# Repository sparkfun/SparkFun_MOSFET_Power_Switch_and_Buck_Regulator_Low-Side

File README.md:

SparkFun MOSFET Power Switch and Buck Regulator (Low-Side)
========================================

[*SparkFun MOSFET Power Switch and Buck Regulator (Low-Side) (COM-23979)*](https://www.sparkfun.com/products/23979)

Does your microcontroller need to control a high-voltage item, like a 12V LED strip, while also needing to be powered? Do you want to avoid having multiple power adapters and microcontrollers for your project? The MOSFET Power Switch and Buck Regulator (Low-Side) is one product we needed at SparkFun, so we figured other folks might have the same problem. Power the board with up to 12V and control up to 10A, all while providing a sweet 3.3V to your control board.

The SparkFun MOSFET Power Switch and Buck Regulator (Low-Side) combines two circuits into one board: an LMR14203 buck regulator configured to output 3.3V and an N-channel MOSFET (PSMN7R0-100BS) configured as a low-side switch. A flyback diode is also on the load side for devices with back EMF! Simply pull the CTL pin low to activate the load.

Various connectors (barrel jack, female header, and poke-home) are provided to connect a power supply to a microcontroller of your choice (Arduino, micro-bit, Raspberry Pi’s microcontroller) and load them together. VCC, 3.3V, CTL, and GND are also broken out through 0.1" spaced PTHs for those who prefer to solder. Two LEDs (PWR_LED and ON_LED) indicate when there is 3.3V and whenever power is applied to the load. Jumpers are included on the back to disable the LEDs. A MEAS PTH jumper is also included for those interested in precisely measuring the current consumption of the system.

_**Note:** While the MOSFET is rated to 100A/100V, we don't recommend you go much above 10A as the PCB polygon pours and traces become the limiter._

Repository Contents
-------------------

* **.github/workflows** -  YAML files used for GitHub Actions and GitHub Pages/mkdocs
* * **/Firmware** - Basic example code to control a load with the MOSFET Power Switch and BUck Regulator
* **/Hardware** - Eagle design files (.brd, .sch)
  * **/Production** - Production panel files (.brd)
* **/docs** - Online documentation files for GitHub Pages and mkdocs
  * **/assets** - Folder containing all the file assets used for product documentation
    * **/board_files** - Copy of design files used for product documentation
    * **/component_documentation** - Datasheets and manuals for hardware components
    * **/img** - Images for product documentation
  * **/github** - Files stating how to contribute and filing issues for product
  * **/javascript** - Folder containing custom javascript used for product documentation
  * **/stylesheet** - Folder containing CSS files used forproduct documentation
* **/overrides** - Customization files used for product documentation
  * **/.icons** - Icons used for product documentation
  * **./partials** - Used for product documentation

Documentation
--------------

* **[Fritzing Part](https://github.com/sparkfun/Fritzing_Parts/blob/main/products/23979_sfe_n-channel_mosfet_power_switch_buck_regulator_low-side_transistor.fzpz)**
* **[Hookup Guide](https://docs.sparkfun.com/SparkFun_MOSFET_Power_Switch_and_Buck_Regulator_Low-Side)** - Basic hookup guide for the MOSFET Power Switch and Buck Regulator (Low-Side).

Product Versions
----------------

* [COM-23979](https://www.sparkfun.com/products/23979) - Initial SparkFun release, v1.1
* [SPX-19799](https://www.sparkfun.com/products/19799) - SparkX version

Version History
---------------
* v1.1 - Initial release

License Information
-------------------

This product is _**open source**_! 

Please review the LICENSE.md file for license information. 

If you have any questions or concerns on licensing, please contact technical support on our [SparkFun forums](https://forum.sparkfun.com/viewforum.php?f=152).

Distributed as-is; no warranty is given.

- Your friends at SparkFun.

_<COLLABORATION CREDIT>_

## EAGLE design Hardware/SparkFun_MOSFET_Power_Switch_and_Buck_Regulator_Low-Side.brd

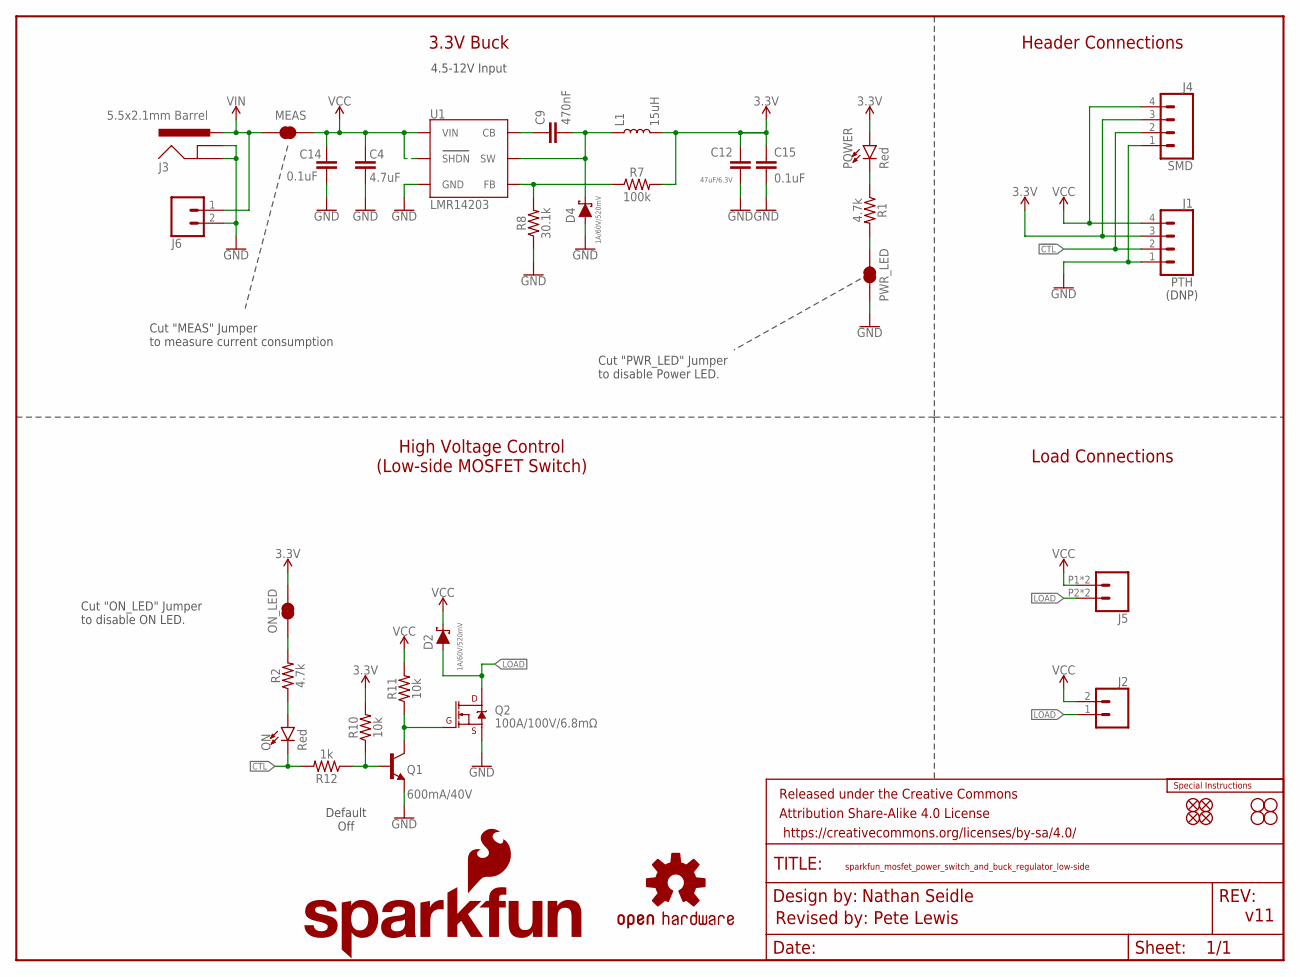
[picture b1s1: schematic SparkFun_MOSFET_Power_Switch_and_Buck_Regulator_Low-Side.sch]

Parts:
C4: 4.7uF; 0603
C9: 470nF; 0603
C12: 47uF/6.3V; 0805
C14, C15: 0.1uF; 0603
D2, D4: 1A/60V/520mV; DIODE-MICRO-SMP
FD1, FD2, FD3, FD4: FIDUCIALUFIDUCIAL; FIDUCIAL-MICRO
FRAME2: FRAME-LETTER; CREATIVE_COMMONS
H1, H2, H3, H4: STAND-OFF
J1: PTH; 1X04_NO_SILK
J2, J6: CONN_021X02_NO_SILK; 1X02_NO_SILK
J3: 5.5x2.1mm Barrel; POWER_JACK_SMD
J4: SMD; 1X04_SMD_VERTICAL_COMBO
J5: CONN_02SMALL_POKEHOME; 1X02_POKEHOME
L1: 15uH; INDUCTOR_LQH32
LOGO1: OSHW-LOGOM; OSHW-LOGO-M
LOGO2: SFE_LOGO_NAME_FLAME.2_INCH; SFE_LOGO_NAME_FLAME_.2
LOGO3: SPECIAL_INSTRUCTIONS-ORDERING; ORDERING_INSTRUCTIONS
MEAS: JUMPER-COMBO_2_NC_TRACE; COMBO-JUMPER_2_NC_TRACE
ON: Red; LED-0603
ON_LED: JUMPER-SMT_2_NC_TRACE_SILK; SMT-JUMPER_2_NC_TRACE_SILK
POWER: Red; LED-0603
PWR_LED: JUMPER-SMT_2_NC_TRACE_SILK; SMT-JUMPER_2_NC_TRACE_SILK
Q1: 600mA/40V; SOT23-3
Q2: 100A/100V/6.8mΩ; TO-263/D2PAK
R1, R2: 4.7k; 0603
R7: 100k; 0603
R8: 30.1k; 0603
R10, R11: 10k; 0603
R12: 1k; 0603
U1: LMR14203; SOT23-6

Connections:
3.3V: C12.1, C15.1, J1.3, J4.3, L1.P$2 (2), ON_LED.2, POWER.A, R7.2, R10.2
!CTL: J1.2, J4.2, ON.C, R12.2
GND: C4.2, C12.2, C14.2, C15.2, D4.A, J1.1, J3.GND (GNDBREAK), J3.P$4 (GND), J4.1, J6.2, PWR_LED.1, Q1.2 (E), Q2.3 (S), R8.1, U1.2 (GND)
LOAD: D2.A, J2.1, J5.P2 (2), J5.P4 (2), Q2.2 (D)
unnamed: Q1.3 (C), Q2.1 (G), R11.1
unnamed: ON.A, R2.1
unnamed: POWER.C, R1.1
unnamed: R7.1, R8.2, U1.3 (FB)
unnamed: PWR_LED.2, R1.2
unnamed: ON_LED.1, R2.2
unnamed: C9.1, U1.1 (CB)
unnamed: Q1.1 (B), R10.1, R12.1
VCC: C4.1, C14.1, D2.C, J1.4, J2.2, J4.4, J5.P1 (1), J5.P3 (1), MEAS.2, MEAS.4 (2), R11.2, U1.4 (SHDN), U1.5 (VIN)
VIN: J3.VIN0 (PWR), J6.1, MEAS.1, MEAS.3 (1)
VSW: C9.2, D4.C, L1.P$1 (1), U1.6 (SW)

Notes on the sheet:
v11
Default Off
Load Connections
High Voltage Control (Low-side MOSFET Switch)
3.3V Buck
4.5-12V Input
Nathan Seidle
Revised by: Pete Lewis
Header Connections
Cut "ON_LED" Jumper to disable ON LED.
Cut "PWR_LED" Jumper to disable Power LED.
(DNP)
Cut "MEAS" Jumper to measure current consumption

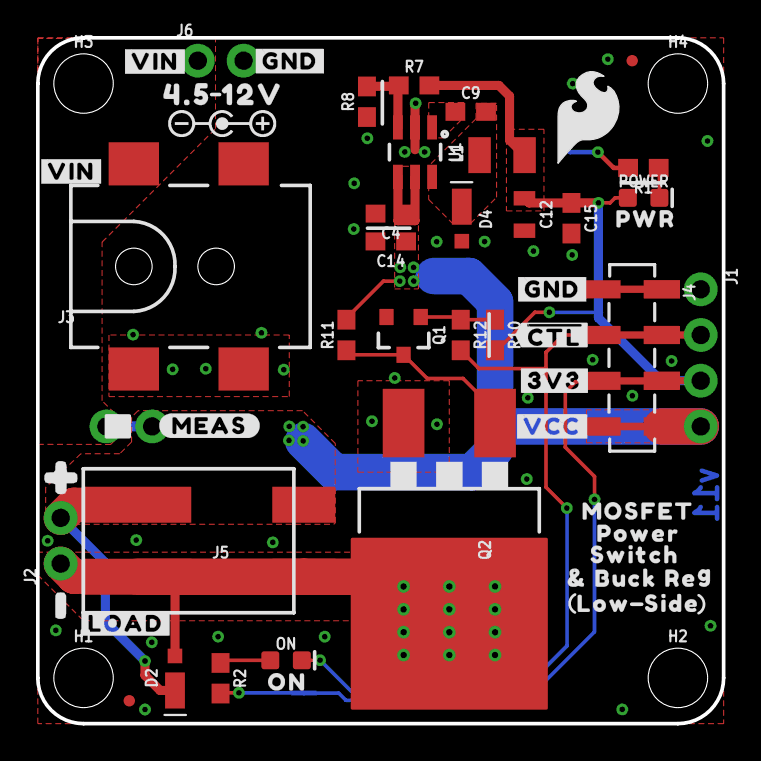
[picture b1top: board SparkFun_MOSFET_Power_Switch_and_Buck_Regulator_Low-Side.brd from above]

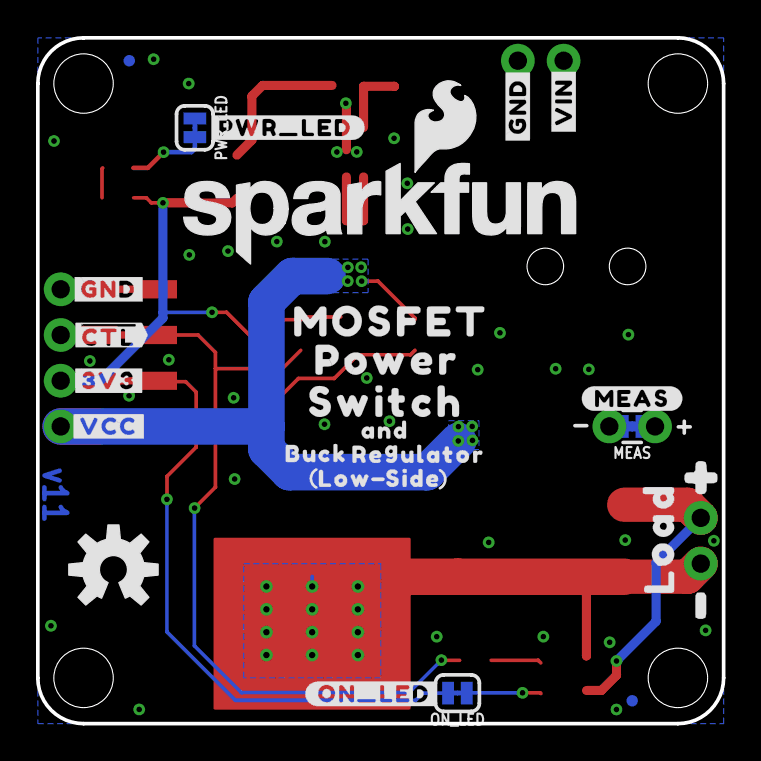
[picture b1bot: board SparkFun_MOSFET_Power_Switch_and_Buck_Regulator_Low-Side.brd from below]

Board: 2 copper layers, 38.1 x 38.1 mm, 83 parts (27 on the bottom side), 15 nets.

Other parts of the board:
U$1: #LOAD#7
U$2: MOSFET0
U$3, U$21, U$36: #VIN#8
U$4, U$6, U$12, U$37: #GND#0
U$8: SFE_LOGO_FLAME_.2
U$9: POWER1
U$10, U$20: #0
U$11, U$22: #1
U$13: SWITCH2
U$14, U$27: #3V3#3
U$15: #PWR_LED#11
U$16: #ON_LED#13
U$17, U$38: #MEAS#14
U$18: 4#5_12V5
U$19: LOAD0
U$23, U$43: LOW0
U$24: MOSFET_0
U$25: POWER_1
U$26: SWITCH_2
U$28: ##CTL##1
U$29: POLARITY_MARKING_CENTER_POSITIVE#JPG
U$30: ##CTL##2
U$31, U$32: #VCC#4
U$33, U$44: SIDE0
U$34: PWR9
U$35: ON10
U$39: BUCK5
U$40: REGULATOR6
U$41: #_BUCK_REG7
U$42: AND8

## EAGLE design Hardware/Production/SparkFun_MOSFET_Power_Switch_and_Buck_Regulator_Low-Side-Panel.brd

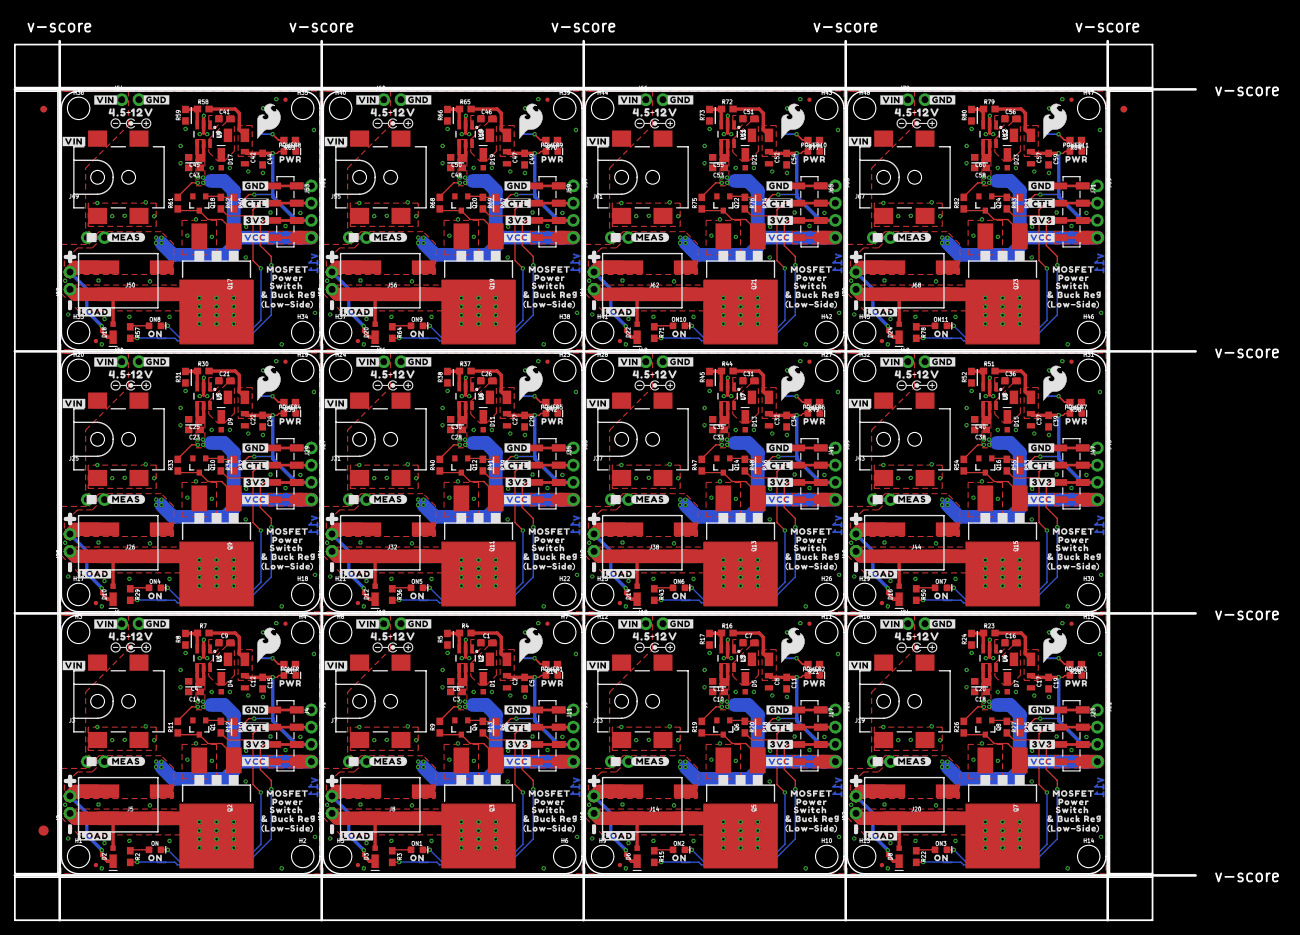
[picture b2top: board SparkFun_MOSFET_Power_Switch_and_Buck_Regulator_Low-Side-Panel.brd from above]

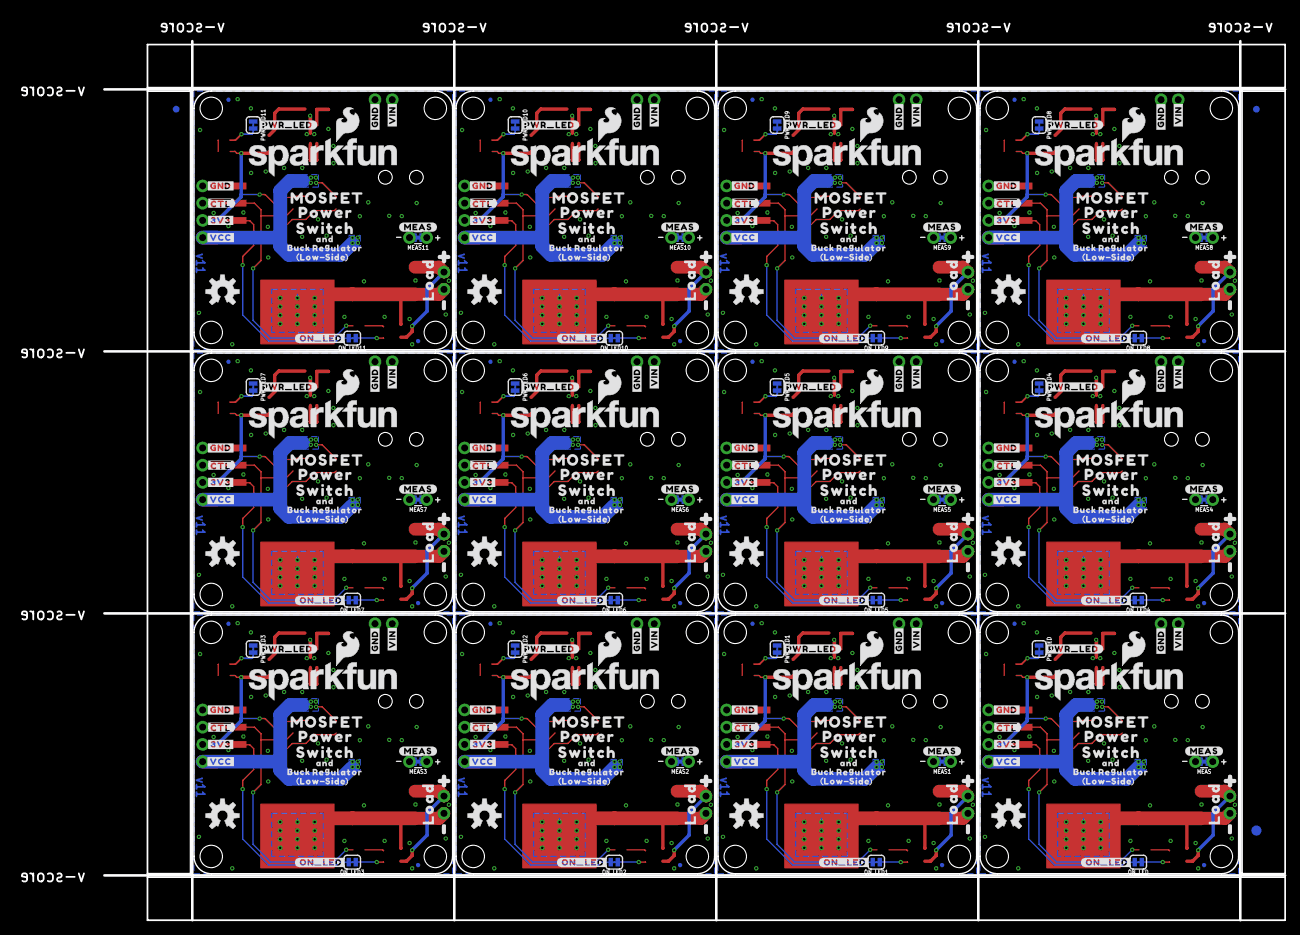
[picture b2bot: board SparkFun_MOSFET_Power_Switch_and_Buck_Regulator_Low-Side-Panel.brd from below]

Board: 2 copper layers, 174.0 x 129.5 mm, 978 parts (327 on the bottom side), 180 nets.

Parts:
C1, C7, C9, C16, C21, C26, C31, C36, C41, C46, C51, C56: 470nF; 0603
C2, C8, C12, C17, C22, C27, C32, C37, C42, C47, C52, C57: 47uF/6.3V; 0805
C3, C5, C10, C11, C14, C15, C18, C19, C23, C24, C28, C29, C33, C34, C38, C39, C43, C44, C48, C49, C53, C54, C58, C59: 0.1uF; 0603
C4, C6, C13, C20, C25, C30, C35, C40, C45, C50, C55, C60: 4.7uF; 0603
D1, D2, D3, D4, D5, D6, D7, D8, D9, D10, D11, D12, D13, D14, D15, D16, D17, D18, D19, D20, D21, D22, D23, D24: 1A/60V/520mV; DIODE-MICRO-SMP
E$1, E$2, E$3, E$4: FIDUCIAL-1X2
E$5, E$6: FIDUCIAL-1.5X3
FD1, FD2, FD3, FD4, FD5, FD6, FD7, FD8, FD9, FD10, FD11, FD12, FD13, FD14, FD15, FD16, FD17, FD18, FD19, FD20, FD21, FD22, FD23, FD24, FD25, FD26, FD27, FD28, FD29, FD30, FD31, FD32, FD33, FD34, FD35, FD36, FD37, FD38, FD39, FD40, FD41, FD42, FD43, FD44, FD45, FD46, FD47, FD48: FIDUCIALUFIDUCIAL; FIDUCIAL-MICRO
H1, H2, H3, H4, H5, H6, H7, H8, H9, H10, H11, H12, H13, H14, H15, H16, H17, H18, H19, H20, H21, H22, H23, H24, H25, H26, H27, H28, H29, H30, H31, H32, H33, H34, H35, H36, H37, H38, H39, H40, H41, H42, H43, H44, H45, H46, H47, H48: STAND-OFF
J1, J9, J15, J21, J27, J33, J39, J45, J51, J57, J63, J69: PTH; 1X04_NO_SILK
J2, J6, J10, J12, J16, J18, J22, J24, J28, J30, J34, J36, J40, J42, J46, J48, J52, J54, J58, J60, J64, J66, J70, J72: 1X02_NO_SILK
J3, J7, J13, J19, J25, J31, J37, J43, J49, J55, J61, J67: 5.5x2.1mm Barrel; POWER_JACK_SMD
J4, J11, J17, J23, J29, J35, J41, J47, J53, J59, J65, J71: SMD; 1X04_SMD_VERTICAL_COMBO
J5, J8, J14, J20, J26, J32, J38, J44, J50, J56, J62, J68: 1X02_POKEHOME
L1, L2, L3, L4, L5, L6, L7, L8, L9, L10, L11, L12: 15uH; INDUCTOR_LQH32
LOGO1, LOGO3, LOGO5, LOGO7, LOGO9, LOGO11, LOGO13, LOGO15, LOGO17, LOGO19, LOGO21, LOGO23: OSHW-LOGOM; OSHW-LOGO-M
LOGO2, LOGO4, LOGO6, LOGO8, LOGO10, LOGO12, LOGO14, LOGO16, LOGO18, LOGO20, LOGO22, LOGO24: SFE_LOGO_NAME_FLAME.2_INCH; SFE_LOGO_NAME_FLAME_.2
MEAS, MEAS1, MEAS2, MEAS3, MEAS4, MEAS5, MEAS6, MEAS7, MEAS8, MEAS9, MEAS10, MEAS11: JUMPER-COMBO_2_NC_TRACE; COMBO-JUMPER_2_NC_TRACE
ON, ON1, ON2, ON3, ON4, ON5, ON6, ON7, ON8, ON9, ON10, ON11: Red; LED-0603
ON_LED, ON_LED1, ON_LED2, ON_LED3, ON_LED4, ON_LED5, ON_LED6, ON_LED7, ON_LED8, ON_LED9, ON_LED10, ON_LED11: SMT-JUMPER_2_NC_TRACE_SILK
POWER, POWER1, POWER2, POWER3, POWER4, POWER5, POWER6, POWER7, POWER8, POWER9, POWER10, POWER11: Red; LED-0603
PWR_LED, PWR_LED1, PWR_LED2, PWR_LED3, PWR_LED4, PWR_LED5, PWR_LED6, PWR_LED7, PWR_LED8, PWR_LED9, PWR_LED10, PWR_LED11: SMT-JUMPER_2_NC_TRACE_SILK
Q1, Q4, Q6, Q8, Q10, Q12, Q14, Q16, Q18, Q20, Q22, Q24: 600mA/40V; SOT23-3
Q2, Q3, Q5, Q7, Q9, Q11, Q13, Q15, Q17, Q19, Q21, Q23: 100A/100V/6.8mΩ; TO-263/D2PAK
R1, R2, R3, R14, R15, R21, R22, R28, R29, R35, R36, R42, R43, R49, R50, R56, R57, R63, R64, R70, R71, R77, R78, R84: 4.7k; 0603
R4, R7, R16, R23, R30, R37, R44, R51, R58, R65, R72, R79: 100k; 0603
R5, R8, R17, R24, R31, R38, R45, R52, R59, R66, R73, R80: 30.1k; 0603
R6, R9, R10, R11, R18, R19, R25, R26, R32, R33, R39, R40, R46, R47, R53, R54, R60, R61, R67, R68, R74, R75, R81, R82: 10k; 0603
R12, R13, R20, R27, R34, R41, R48, R55, R62, R69, R76, R83: 1k; 0603
U1, U2, U3, U4, U5, U6, U7, U8, U9, U10, U11, U12: LMR14203; SOT23-6
U$1, U$63, U$105, U$147, U$189, U$231, U$273, U$315, U$357, U$399, U$441, U$483: #LOAD#7
U$2, U$49, U$91, U$133, U$175, U$217, U$259, U$301, U$343, U$385, U$427, U$469: MOSFET0
U$3, U$21, U$36, U$64, U$71, U$75, U$106, U$113, U$117, U$148, U$155, U$159, U$190, U$197, U$201, U$232, U$239, U$243, U$274, U$281, U$285, U$316, U$323, U$327, U$358, U$365, U$369, U$400, U$407, U$411, U$442, U$449, U$453, U$484, U$491, U$495: #VIN#8
U$4, U$6, U$12, U$37, U$55, U$56, U$72, U$74, U$97, U$98, U$114, U$116, U$139, U$140, U$156, U$158, U$181, U$182, U$198, U$200, U$223, U$224, U$240, U$242, U$265, U$266, U$282, U$284, U$307, U$308, U$324, U$326, U$349, U$350, U$366, U$368, U$391, U$392, U$408, U$410, U$433, U$434, U$450, U$452, U$475, U$476, U$492, U$494: #GND#0
U$5, U$29, U$85, U$127, U$169, U$211, U$253, U$295, U$337, U$379, U$421, U$463: POLARITY_MARKING_CENTER_POSITIVE#JPG
U$7, U$10, U$20, U$47, U$86, U$89, U$128, U$131, U$170, U$173, U$212, U$215, U$254, U$257, U$296, U$299, U$338, U$341, U$380, U$383, U$422, U$425, U$464, U$467: #0
U$8, U$65, U$107, U$149, U$191, U$233, U$275, U$317, U$359, U$401, U$443, U$485: SFE_LOGO_FLAME_.2
U$9, U$50, U$92, U$134, U$176, U$218, U$260, U$302, U$344, U$386, U$428, U$470: POWER1
U$11, U$22, U$45, U$48, U$87, U$90, U$129, U$132, U$171, U$174, U$213, U$216, U$255, U$258, U$297, U$300, U$339, U$342, U$381, U$384, U$423, U$426, U$465, U$468: #1
U$13, U$51, U$93, U$135, U$177, U$219, U$261, U$303, U$345, U$387, U$429, U$471: SWITCH2
U$14, U$27, U$59, U$60, U$101, U$102, U$143, U$144, U$185, U$186, U$227, U$228, U$269, U$270, U$311, U$312, U$353, U$354, U$395, U$396, U$437, U$438, U$479, U$480: #3V3#3
U$15, U$66, U$108, U$150, U$192, U$234, U$276, U$318, U$360, U$402, U$444, U$486: #PWR_LED#11
U$16, U$67, U$109, U$151, U$193, U$235, U$277, U$319, U$361, U$403, U$445, U$487: #ON_LED#13
U$17, U$38, U$68, U$76, U$110, U$118, U$152, U$160, U$194, U$202, U$236, U$244, U$278, U$286, U$320, U$328, U$362, U$370, U$404, U$412, U$446, U$454, U$488, U$496: #MEAS#14
U$18, U$73, U$115, U$157, U$199, U$241, U$283, U$325, U$367, U$409, U$451, U$493: 4#5_12V5
U$19, U$46, U$88, U$130, U$172, U$214, U$256, U$298, U$340, U$382, U$424, U$466: LOAD0
U$23, U$43, U$69, U$81, U$111, U$123, U$153, U$165, U$195, U$207, U$237, U$249, U$279, U$291, U$321, U$333, U$363, U$375, U$405, U$417, U$447, U$459, U$489, U$501: LOW0
U$24, U$52, U$94, U$136, U$178, U$220, U$262, U$304, U$346, U$388, U$430, U$472: MOSFET_0
U$25, U$53, U$95, U$137, U$179, U$221, U$263, U$305, U$347, U$389, U$431, U$473: POWER_1
U$26, U$54, U$96, U$138, U$180, U$222, U$264, U$306, U$348, U$390, U$432, U$474: SWITCH_2
U$28, U$57, U$99, U$141, U$183, U$225, U$267, U$309, U$351, U$393, U$435, U$477: ##CTL##1
U$30, U$58, U$100, U$142, U$184, U$226, U$268, U$310, U$352, U$394, U$436, U$478: ##CTL##2
U$31, U$32, U$61, U$62, U$103, U$104, U$145, U$146, U$187, U$188, U$229, U$230, U$271, U$272, U$313, U$314, U$355, U$356, U$397, U$398, U$439, U$440, U$481, U$482: #VCC#4
U$33, U$44, U$70, U$82, U$112, U$124, U$154, U$166, U$196, U$208, U$238, U$250, U$280, U$292, U$322, U$334, U$364, U$376, U$406, U$418, U$448, U$460, U$490, U$502: SIDE0
U$34, U$83, U$125, U$167, U$209, U$251, U$293, U$335, U$377, U$419, U$461, U$503: PWR9
U$35, U$84, U$126, U$168, U$210, U$252, U$294, U$336, U$378, U$420, U$462, U$504: ON10
U$39, U$77, U$119, U$161, U$203, U$245, U$287, U$329, U$371, U$413, U$455, U$497: BUCK5
U$40, U$78, U$120, U$162, U$204, U$246, U$288, U$330, U$372, U$414, U$456, U$498: REGULATOR6
U$41, U$79, U$121, U$163, U$205, U$247, U$289, U$331, U$373, U$415, U$457, U$499: #_BUCK_REG7
U$42, U$80, U$122, U$164, U$206, U$248, U$290, U$332, U$374, U$416, U$458, U$500: AND8

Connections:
3.3V: C12.1, C15.1, J1.3, J4.3, L1.P$2, ON_LED.2, POWER.A, R7.2, R10.2
3.3V1: C2.1, C5.1, J9.3, J11.3, L2.P$2, ON_LED1.2, POWER1.A, R4.2, R6.2
3.3V2: C8.1, C11.1, J15.3, J17.3, L3.P$2, ON_LED2.2, POWER2.A, R16.2, R18.2
3.3V3: C17.1, C19.1, J21.3, J23.3, L4.P$2, ON_LED3.2, POWER3.A, R23.2, R25.2
3.3V4: C22.1, C24.1, J27.3, J29.3, L5.P$2, ON_LED4.2, POWER4.A, R30.2, R32.2
3.3V5: C27.1, C29.1, J33.3, J35.3, L6.P$2, ON_LED5.2, POWER5.A, R37.2, R39.2
3.3V6: C32.1, C34.1, J39.3, J41.3, L7.P$2, ON_LED6.2, POWER6.A, R44.2, R46.2
3.3V7: C37.1, C39.1, J45.3, J47.3, L8.P$2, ON_LED7.2, POWER7.A, R51.2, R53.2
3.3V8: C42.1, C44.1, J51.3, J53.3, L9.P$2, ON_LED8.2, POWER8.A, R58.2, R60.2
3.3V9: C47.1, C49.1, J57.3, J59.3, L10.P$2, ON_LED9.2, POWER9.A, R65.2, R67.2
3.3V10: C52.1, C54.1, J63.3, J65.3, L11.P$2, ON_LED10.2, POWER10.A, R72.2, R74.2
3.3V11: C57.1, C59.1, J69.3, J71.3, L12.P$2, ON_LED11.2, POWER11.A, R79.2, R81.2
!CTL: J1.2, J4.2, ON.C, R12.2
!CTL1: J9.2, J11.2, ON1.C, R13.2
!CTL2: J15.2, J17.2, ON2.C, R20.2
!CTL3: J21.2, J23.2, ON3.C, R27.2
!CTL4: J27.2, J29.2, ON4.C, R34.2
!CTL5: J33.2, J35.2, ON5.C, R41.2
!CTL6: J39.2, J41.2, ON6.C, R48.2
!CTL7: J45.2, J47.2, ON7.C, R55.2
!CTL8: J51.2, J53.2, ON8.C, R62.2
!CTL9: J57.2, J59.2, ON9.C, R69.2
!CTL10: J63.2, J65.2, ON10.C, R76.2
!CTL11: J69.2, J71.2, ON11.C, R83.2
GND: C4.2, C12.2, C14.2, C15.2, D4.A, J1.1, J3.GND, J3.P$4, J4.1, J6.2, PWR_LED.1, Q1.2, Q2.3, R8.1, U1.2
GND1: C2.2, C3.2, C5.2, C6.2, D1.A, J7.GND, J7.P$4, J9.1, J11.1, J12.2, PWR_LED1.1, Q3.3, Q4.2, R5.1, U2.2
GND2: C8.2, C10.2, C11.2, C13.2, D5.A, J13.GND, J13.P$4, J15.1, J17.1, J18.2, PWR_LED2.1, Q5.3, Q6.2, R17.1, U3.2
GND3: C17.2, C18.2, C19.2, C20.2, D7.A, J19.GND, J19.P$4, J21.1, J23.1, J24.2, PWR_LED3.1, Q7.3, Q8.2, R24.1, U4.2
GND4: C22.2, C23.2, C24.2, C25.2, D9.A, J25.GND, J25.P$4, J27.1, J29.1, J30.2, PWR_LED4.1, Q9.3, Q10.2, R31.1, U5.2
GND5: C27.2, C28.2, C29.2, C30.2, D11.A, J31.GND, J31.P$4, J33.1, J35.1, J36.2, PWR_LED5.1, Q11.3, Q12.2, R38.1, U6.2
GND6: C32.2, C33.2, C34.2, C35.2, D13.A, J37.GND, J37.P$4, J39.1, J41.1, J42.2, PWR_LED6.1, Q13.3, Q14.2, R45.1, U7.2
GND7: C37.2, C38.2, C39.2, C40.2, D15.A, J43.GND, J43.P$4, J45.1, J47.1, J48.2, PWR_LED7.1, Q15.3, Q16.2, R52.1, U8.2
GND8: C42.2, C43.2, C44.2, C45.2, D17.A, J49.GND, J49.P$4, J51.1, J53.1, J54.2, PWR_LED8.1, Q17.3, Q18.2, R59.1, U9.2
GND9: C47.2, C48.2, C49.2, C50.2, D19.A, J55.GND, J55.P$4, J57.1, J59.1, J60.2, PWR_LED9.1, Q19.3, Q20.2, R66.1, U10.2
GND10: C52.2, C53.2, C54.2, C55.2, D21.A, J61.GND, J61.P$4, J63.1, J65.1, J66.2, PWR_LED10.1, Q21.3, Q22.2, R73.1, U11.2
GND11: C57.2, C58.2, C59.2, C60.2, D23.A, J67.GND, J67.P$4, J69.1, J71.1, J72.2, PWR_LED11.1, Q23.3, Q24.2, R80.1, U12.2
LOAD: D2.A, J2.1, J5.P2, J5.P4, Q2.2
LOAD1: D3.A, J8.P2, J8.P4, J10.1, Q3.2
LOAD2: D6.A, J14.P2, J14.P4, J16.1, Q5.2
LOAD3: D8.A, J20.P2, J20.P4, J22.1, Q7.2
LOAD4: D10.A, J26.P2, J26.P4, J28.1, Q9.2
LOAD5: D12.A, J32.P2, J32.P4, J34.1, Q11.2
LOAD6: D14.A, J38.P2, J38.P4, J40.1, Q13.2
LOAD7: D16.A, J44.P2, J44.P4, J46.1, Q15.2
LOAD8: D18.A, J50.P2, J50.P4, J52.1, Q17.2
LOAD9: D20.A, J56.P2, J56.P4, J58.1, Q19.2
LOAD10: D22.A, J62.P2, J62.P4, J64.1, Q21.2
LOAD11: D24.A, J68.P2, J68.P4, J70.1, Q23.2
unnamed: Q1.3, Q2.1, R11.1
unnamed: ON.A, R2.1
unnamed: POWER.C, R1.1
unnamed: ON1.A, R3.1
unnamed: R7.1, R8.2, U1.3
unnamed: PWR_LED.2, R1.2
unnamed: ON_LED.1, R2.2
unnamed: R4.1, R5.2, U2.3
unnamed: C1.1, U2.1
unnamed: C9.1, U1.1
unnamed: Q3.1, Q4.3, R9.1
unnamed: Q1.1, R10.1, R12.1
unnamed: Q4.1, R6.1, R13.1
unnamed: POWER1.C, R14.1
unnamed: PWR_LED1.2, R14.2
unnamed: ON_LED1.1, R3.2
unnamed: ON2.A, R15.1
unnamed: R16.1, R17.2, U3.3
unnamed: C7.1, U3.1
unnamed: Q5.1, Q6.3, R19.1
unnamed: Q6.1, R18.1, R20.1
unnamed: POWER2.C, R21.1
unnamed: PWR_LED2.2, R21.2
unnamed: ON_LED2.1, R15.2
unnamed: ON3.A, R22.1
unnamed: R23.1, R24.2, U4.3
unnamed: C16.1, U4.1
unnamed: Q7.1, Q8.3, R26.1
unnamed: Q8.1, R25.1, R27.1
unnamed: POWER3.C, R28.1
unnamed: PWR_LED3.2, R28.2
unnamed: ON_LED3.1, R22.2
unnamed: ON4.A, R29.1
unnamed: R30.1, R31.2, U5.3
unnamed: C21.1, U5.1
unnamed: Q9.1, Q10.3, R33.1
unnamed: Q10.1, R32.1, R34.1
unnamed: POWER4.C, R35.1
unnamed: PWR_LED4.2, R35.2
unnamed: ON_LED4.1, R29.2
unnamed: ON5.A, R36.1
unnamed: R37.1, R38.2, U6.3
unnamed: C26.1, U6.1
unnamed: Q11.1, Q12.3, R40.1
unnamed: Q12.1, R39.1, R41.1
unnamed: POWER5.C, R42.1
unnamed: PWR_LED5.2, R42.2
unnamed: ON_LED5.1, R36.2
unnamed: ON6.A, R43.1
unnamed: R44.1, R45.2, U7.3
unnamed: C31.1, U7.1
unnamed: Q13.1, Q14.3, R47.1
unnamed: Q14.1, R46.1, R48.1
unnamed: POWER6.C, R49.1
unnamed: PWR_LED6.2, R49.2
unnamed: ON_LED6.1, R43.2
unnamed: ON7.A, R50.1
unnamed: R51.1, R52.2, U8.3
unnamed: C36.1, U8.1
unnamed: Q15.1, Q16.3, R54.1
unnamed: Q16.1, R53.1, R55.1
unnamed: POWER7.C, R56.1
unnamed: PWR_LED7.2, R56.2
unnamed: ON_LED7.1, R50.2
unnamed: ON8.A, R57.1
unnamed: R58.1, R59.2, U9.3
unnamed: C41.1, U9.1
unnamed: Q17.1, Q18.3, R61.1
unnamed: Q18.1, R60.1, R62.1
unnamed: POWER8.C, R63.1
unnamed: PWR_LED8.2, R63.2
unnamed: ON_LED8.1, R57.2
unnamed: ON9.A, R64.1
unnamed: R65.1, R66.2, U10.3
unnamed: C46.1, U10.1
unnamed: Q19.1, Q20.3, R68.1
unnamed: Q20.1, R67.1, R69.1
unnamed: POWER9.C, R70.1
unnamed: PWR_LED9.2, R70.2
unnamed: ON_LED9.1, R64.2
unnamed: ON10.A, R71.1
unnamed: R72.1, R73.2, U11.3
unnamed: C51.1, U11.1
unnamed: Q21.1, Q22.3, R75.1
unnamed: Q22.1, R74.1, R76.1
unnamed: POWER10.C, R77.1
unnamed: PWR_LED10.2, R77.2
unnamed: ON_LED10.1, R71.2
unnamed: ON11.A, R78.1
unnamed: R79.1, R80.2, U12.3
unnamed: C56.1, U12.1
unnamed: Q23.1, Q24.3, R82.1
unnamed: Q24.1, R81.1, R83.1
unnamed: POWER11.C, R84.1
unnamed: PWR_LED11.2, R84.2
unnamed: ON_LED11.1, R78.2
VCC: C4.1, C14.1, D2.C, J1.4, J2.2, J4.4, J5.P1, J5.P3, MEAS.2, MEAS.4, R11.2, U1.4, U1.5
VCC1: C3.1, C6.1, D3.C, J8.P1, J8.P3, J9.4, J10.2, J11.4, MEAS1.2, MEAS1.4, R9.2, U2.4, U2.5
VCC2: C10.1, C13.1, D6.C, J14.P1, J14.P3, J15.4, J16.2, J17.4, MEAS2.2, MEAS2.4, R19.2, U3.4, U3.5
VCC3: C18.1, C20.1, D8.C, J20.P1, J20.P3, J21.4, J22.2, J23.4, MEAS3.2, MEAS3.4, R26.2, U4.4, U4.5
VCC4: C23.1, C25.1, D10.C, J26.P1, J26.P3, J27.4, J28.2, J29.4, MEAS4.2, MEAS4.4, R33.2, U5.4, U5.5
VCC5: C28.1, C30.1, D12.C, J32.P1, J32.P3, J33.4, J34.2, J35.4, MEAS5.2, MEAS5.4, R40.2, U6.4, U6.5
VCC6: C33.1, C35.1, D14.C, J38.P1, J38.P3, J39.4, J40.2, J41.4, MEAS6.2, MEAS6.4, R47.2, U7.4, U7.5
VCC7: C38.1, C40.1, D16.C, J44.P1, J44.P3, J45.4, J46.2, J47.4, MEAS7.2, MEAS7.4, R54.2, U8.4, U8.5
VCC8: C43.1, C45.1, D18.C, J50.P1, J50.P3, J51.4, J52.2, J53.4, MEAS8.2, MEAS8.4, R61.2, U9.4, U9.5
VCC9: C48.1, C50.1, D20.C, J56.P1, J56.P3, J57.4, J58.2, J59.4, MEAS9.2, MEAS9.4, R68.2, U10.4, U10.5
VCC10: C53.1, C55.1, D22.C, J62.P1, J62.P3, J63.4, J64.2, J65.4, MEAS10.2, MEAS10.4, R75.2, U11.4, U11.5
VCC11: C58.1, C60.1, D24.C, J68.P1, J68.P3, J69.4, J70.2, J71.4, MEAS11.2, MEAS11.4, R82.2, U12.4, U12.5
VIN: J3.VIN0, J6.1, MEAS.1, MEAS.3
VIN1: J7.VIN0, J12.1, MEAS1.1, MEAS1.3
VIN2: J13.VIN0, J18.1, MEAS2.1, MEAS2.3
VIN3: J19.VIN0, J24.1, MEAS3.1, MEAS3.3
VIN4: J25.VIN0, J30.1, MEAS4.1, MEAS4.3
VIN5: J31.VIN0, J36.1, MEAS5.1, MEAS5.3
VIN6: J37.VIN0, J42.1, MEAS6.1, MEAS6.3
VIN7: J43.VIN0, J48.1, MEAS7.1, MEAS7.3
VIN8: J49.VIN0, J54.1, MEAS8.1, MEAS8.3
VIN9: J55.VIN0, J60.1, MEAS9.1, MEAS9.3
VIN10: J61.VIN0, J66.1, MEAS10.1, MEAS10.3
VIN11: J67.VIN0, J72.1, MEAS11.1, MEAS11.3
VSW: C9.2, D4.C, L1.P$1, U1.6
VSW1: C1.2, D1.C, L2.P$1, U2.6
VSW2: C7.2, D5.C, L3.P$1, U3.6
VSW3: C16.2, D7.C, L4.P$1, U4.6
VSW4: C21.2, D9.C, L5.P$1, U5.6
VSW5: C26.2, D11.C, L6.P$1, U6.6
VSW6: C31.2, D13.C, L7.P$1, U7.6
VSW7: C36.2, D15.C, L8.P$1, U8.6
VSW8: C41.2, D17.C, L9.P$1, U9.6
VSW9: C46.2, D19.C, L10.P$1, U10.6
VSW10: C51.2, D21.C, L11.P$1, U11.6
VSW11: C56.2, D23.C, L12.P$1, U12.6

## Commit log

2023-10-09 Original SparkX hardware files (v10)
2023-10-12 add 4-pin female header
    -added SMD vertical 4-pin header to allow solderless connection access to the CTRL line and more.
    -Added jumpers to kill power and on LEDs
    -updated silk to inverted buzzard style
    -changed logo to SFE
    -updated measures.
2023-10-13 Buck reg routing
    -optimized buck reg routing
    -added PTH header for VIN/GND
    -added "low-side" to silk name top and bottom
2023-10-13 MOSFET datasheet
2023-10-13 updated to new KB red resistor
    -updated red led and limiting resistor
2023-10-13 Re-routed Flyback Diode circuit
2023-10-17 Group Review mods round one
    -Powered ON LED from 3.3V and controlled via CTL net.
    -Moved GND/VIN PTH headers away from under the barrel jack for easier access
    -routed some of load path with polygons to avoid sharp 90 degree turns in traces
    -moved MEAS jumper to allow direct GND pour path from MOSFET to Barrel jack GND pads
    -added "+" and "-" silk to MEAS jumper PTH header
    -enlarged board to 1.5" square shape
2023-10-17 BOM consolidation
    -made the two 0.1uF caps the same one (100V).
    -Enlarged LOAD net trace/connection with polygon.
2023-10-18 renaming files to match product name
2023-10-18 Update silk to match product name
2023-10-18 sch cleanup
    -moved INPUT range to just below the “3.3V Buck” section title.
2023-10-18 Added D1 Zener
    -Added D1 to clamp spike on VCC and protect U1 and C4
2023-10-18 approved DRC overlap errors on jumpers
2023-10-18 text overlap in sch
2023-10-18 group review final changes
    -moved 4-pin header north 0.05inch to get all headers on same grid for perf board plug in ability.
    -MEAS moved to on grid.
    -upped material quality to TG155
    -LED labels to text only style silk
    -added exposed copper for heat sink under the MOSFET
2023-10-19 Removed D1 Zener
2023-10-19 checklist run eng
    -sch tightening and cleanup
    -nudged some vias to avoid cutting silk in bottom logo
2023-10-19 production panel and gerbers v11
2023-10-23 Fix minor spelling error in schematic's note. =)
2023-10-23 Adjusted ordering instructions to TG135
2024-01-15 updated Q1 and R11
    -Q1 is now an NCH MOSFET
    -R11 is increased to 100K to save power when things are turned off.
2024-02-09 Initial GitHub Pages Tutorial to Main
2024-02-09 Deployed d37de76 with MkDocs version: 1.5.3
2024-10-28 Add cookies
2024-10-29 Deployed 7b4ae9d with MkDocs version: 1.6.1
2026-06-03 Deployed 667aa8e with MkDocs version: 1.6.1

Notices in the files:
parts and their libraries:
SparkFun-Aesthetics: Licensing: Creative Commons ShareAlike 4.0 International - https://creativecommons.org/licenses/by-sa/4.0
SparkFun-Aesthetics: Released under the Creative Commons Attribution Share-Alike 4.0 License
SparkFun-Aesthetics: https://creativecommons.org/licenses/by-sa/4.0
